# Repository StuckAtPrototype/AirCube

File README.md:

# AirCube

**See your air.** AirCube is a desktop air quality monitor with built-in **Home Assistant** support over **Zigbee** or **Bluetooth (BLE)**. Every model tracks temperature, humidity, eCO2, eTVOC, and VOC Level; AirCube Pro also measures true CO2 and ambient light. A glanceable LED shows the current air quality.

Works standalone out of the box. Pairs with Home Assistant in minutes. Other platforms are supported through **[community-contributed extensions](#community-extensions)**.

[AirCube Web](https://stuckatprototype.github.io/AirCube/) -- Live readings, history and firmware updates in your browser. Nothing to install.

[Watch the overview](https://www.youtube.com/watch?v=a4EFVtmDL8s) -- What AirCube does and why it's open source, in under three minutes.

[StuckAtPrototype Labs](https://www.youtube.com/@StuckAtPrototypeLabs) -- Step-by-step video walkthroughs: [ZHA setup](https://www.youtube.com/watch?v=rpkR3O64rY8), [Zigbee2MQTT setup](https://www.youtube.com/watch?v=eybU8-ZFDcc), and [updating firmware from the browser](https://www.youtube.com/watch?v=4XfEABJolAE).

[AirCube](https://stuckatprototype.com/products/aircube) -- Assembled AirCube

[AirCube Populated PCB](https://stuckatprototype.com/products/aircube-populated-pcb) -- AirCube Populated PCB

---

## Getting Started

**1. Plug it in** -- Connect the USB-C cable to any USB port or charger. AirCube powers on automatically.

**2. Wait for warm-up** -- The air quality sensor needs about 3 minutes to stabilize after power-on. During this time, the LED may not reflect accurate readings.

**3. Read the color** -- Once warmed up, the LED tells you everything:

| LED Color | Air Quality |
|-----------|------------|
| Green | Good |
| Yellow | Moderate |
| Orange | Poor |
| Red | Bad -- consider ventilating |

The color shifts smoothly as conditions change. No app needed -- just glance at it.

> **Firmware 1.5.0 and above** drive the LED from **canonical VOC Level** (TVOC-derived, absolute). The color is a smooth green-to-red gradient -- same feel as older firmware, but tied to fixed indoor-air bands instead of the relative AQI-S baseline. See **[LED Reference](#led-reference)** for the exact mapping. Firmware **1.4.3 and below** used the same gradient shape, but driven by **AQI-S** instead.

**4. Adjust brightness** -- Press the button to cycle through brightness levels.

That's it. AirCube works out of the box with no setup, no accounts, and no Wi-Fi.

---

## Base vs. Pro

Both models use the ScioSense ENS161 for VOC Level, eCO2, and eTVOC. Choose **Pro** when you also want a direct CO2 measurement and automatic LED dimming based on room light.

| Feature | Base | Pro |
|---------|------|-----|
| VOC Level, eCO2, and eTVOC | ENS161 | ENS161 |
| Temperature and humidity | ENS210 | Sensirion SCD41 |
| True CO2 | -- | Sensirion SCD41 (NDIR) |
| Ambient light | -- | VCNL4040 |
| Automatic LED dimming | -- | Yes |
| LED air-quality source | VOC Level | Whichever is worse: VOC Level or true CO2 |

> **eCO2 vs. true CO2:** eCO2 is an estimate derived from detected VOCs. The Pro's SCD41 measures CO2 directly using NDIR, while the ENS161 still detects odors and fumes that a pure CO2 sensor can miss.

## What AirCube Measures

| Measurement | Range | What It Tells You |
|-------------|-------|------------------|
| **VOC Level** | 0 -- 500 | TVOC-derived score against fixed indoor-air bands (firmware 1.5.0+; 0--500 scale in 1.5.1+) |
| **AQI-S** (deprecated) | -- | Legacy relative VOC score. As of firmware 1.5.0 this always reports **0** over USB serial -- kept only for compatibility. Use VOC Level instead. |
| **eCO2** (equivalent CO2) | 400 -- 65,000 ppm | Estimated CO2 level derived from detected VOCs |
| **CO2** (Pro only) | 400 -- 5,000 ppm | True CO2 concentration from the SCD41 (direct NDIR measurement) |
| **eTVOC** (equivalent Total VOC) | 0 -- 65,000 ppb | Total volatile organic compound concentration |
| **Temperature** | | Room temperature in Celsius |
| **Humidity** | 0 -- 100 % | Relative humidity percentage |
| **Illuminance** (Pro only) | | Ambient light in lux; also used to dim the LED automatically |

### Understanding the readings

AirCube Base uses a **ScioSense ENS161** gas sensor and an **ENS210** temperature/humidity sensor. AirCube Pro uses the ENS161 alongside an **SCD41** for true CO2, temperature, and humidity, plus a **VCNL4040** ambient light sensor.

**eCO2 (ppm)** -- Estimated CO2 derived from detected VOCs, not a direct CO2 measurement. Useful for judging ventilation; also picks up odors and fumes a pure CO2 sensor would miss.

**eTVOC (ppb)** -- Total volatile organic compounds in the air. Spikes after cooking or cleaning are normal; sustained high readings mean you should ventilate.

**VOC Level (0--500)** -- TVOC mapped to a fixed indoor-air scale (firmware 1.5.1+). Linear ramp between band edges; TVOC-only (eCO2 does not affect VOC Level). Reported over Zigbee and USB serial.

| Rating | LED color | VOC Level | TVOC (ppb) |
|--------|-----------|-----|------------|
| Excellent | Green | 0 -- 15 | 0 -- 65 |
| Good | Green → lime | 15 -- 50 | 65 -- 220 |
| Moderate | Lime → yellow | 50 -- 100 | 220 -- 650 |
| Poor | Yellow → orange → red | 100 -- 200 | 650 -- 2,200 |
| Unhealthy | Red | 200 -- 500 | 2,200 -- 5,500 |

On Base hardware, the LED color is derived from TVOC/VOC Level alone (eCO2 does not drive the LED). VOC Level is linear between band edges, so the LED fades smoothly. See below for Pro's CO2 arbitration.

**AQI-S (deprecated, USB serial only)** -- A legacy ScioSense relative score from firmware before 1.5.0. As of firmware 1.5.0, AQI-S is deprecated and always reports **0** -- it's kept in the serial output only for compatibility with older tools. Use **VOC Level**, **eCO2**/**eTVOC**, or true **CO2** (Pro) instead.

**VOC Level** drives the LED color on Base hardware. On **Pro**, the LED shows whichever is worse -- VOC Level or CO2 Level (from the true CO2 reading). See **[LED Reference](#led-reference)**.

### Warm-up and initial start-up

The ENS161 needs about **3 minutes** of warm-up in standard mode before readings stabilize. On the very first power-on of a new sensor the initial start-up takes about **1 hour** as the sensor conditions itself. Readings during these periods may be inaccurate -- the LED and status flag will indicate when the sensor is ready.

---

## Built-in vs. community

**Maintained by StuckAtPrototype:** firmware, hardware, desktop app, and the **Home Assistant** integration documented in **[HOME_ASSISTANT.md](HOME_ASSISTANT.md)**.

**Community-contributed:** integrations built and shared by the community. They live in this repo and are welcome, but StuckAtPrototype does not test or ship them. They may require extra setup and can break when a vendor updates their platform. See **[Community extensions](#community-extensions)**.

---

## Home Assistant Integration

AirCube was designed for Home Assistant. It connects over **Zigbee** -- no USB cable to your server, no cloud, no Wi-Fi credentials to configure. Plug it in, hold the button for 3 seconds to start pairing, and six core entities show up: temperature, humidity, eCO2, eTVOC, VOC Level, and brightness.

**AirCube Pro** adds two more: **true CO2** (SCD41) and **illuminance** (VCNL4040). Both are exposed in **ZHA** and **Zigbee2MQTT 2.x** -- eight entities total on a Pro.

Once connected you can:
- **Track air quality over time** with built-in history graphs
- **Set up automations** -- turn on a fan when eCO2 gets too high, send a notification when VOC Level spikes
- **Monitor every room** -- each AirCube pairs independently, name them however you like

**You'll need:** a Zigbee coordinator dongle (we recommend the [SONOFF ZBDongle-E](https://sonoff.tech/product/gateway-and-sensors/sonoff-zigbee-3-0-usb-dongle-plus-e/), ~$13) plugged into your Home Assistant machine.

**Works with** ZHA (built-in) and Zigbee2MQTT.

**Video walkthroughs:** [Set up AirCube with ZHA](https://www.youtube.com/watch?v=rpkR3O64rY8) · [Set up AirCube with Zigbee2MQTT](https://www.youtube.com/watch?v=eybU8-ZFDcc)

**Full setup guide:** **[Connecting AirCube to Home Assistant](HOME_ASSISTANT.md)**

### No Zigbee dongle? AirCube also works over Bluetooth

AirCube boots into **BLE mode** by default (until you pair it to Zigbee) and broadcasts standard
**BTHome** data -- temperature, humidity, CO2, and TVOC. If your Home Assistant instance has a
Bluetooth adapter or an [ESPHome Bluetooth proxy](https://esphome.io/components/bluetooth_proxy.html)
nearby, it can often pick up these readings passively, with no pairing step and no Zigbee hardware
at all. Building a custom BLE client? See the **[BLE GATT Protocol reference](docs/BLE_GATT_PROTOCOL.md)**.

---

## Community extensions

The integrations below are **community-contributed**. They are not maintained by StuckAtPrototype and compatibility with vendor hub or app updates is not guaranteed.

### SmartThings (Samsung Zigbee hub) — community-contributed

Some users run AirCube on a **Samsung SmartThings** Zigbee hub over **Zigbee** (no Wi-Fi configuration on the device). The hub must support **SmartThings Edge**.

By default, the SmartThings app may only show **temperature** and **humidity** until you install the community **AirCube Zigbee** Edge driver from this repository and assign it to the device.

**Full setup guide:** **[Connecting AirCube to SmartThings](SMARTTHINGS.md)** (pairing, SmartThings CLI, driver channel, verification in the app and [Advanced Web App](https://my.smartthings.com/advanced)).

**Troubleshooting:** If you only see temperature and humidity, install the **AirCube Zigbee** Edge driver from [`smartthings/aircube-zigbee/`](smartthings/aircube-zigbee/) and assign it to the device. Details are in **[SMARTTHINGS.md](SMARTTHINGS.md)**.

---

## Connect to Your Computer

Plug the AirCube into your computer with a **data-capable USB-C cable** to see live readings, charts, and history.

### In your browser -- nothing to install

**[AirCube Web](https://stuckatprototype.github.io/AirCube/)** connects over USB straight from Chrome or Edge: live readings, LED brightness, history with CSV export, and firmware updates. Click **Connect**, pick your cube, and you're in.

### Download the app

Check the [Releases](https://github.com/StuckAtPrototype/AirCube/releases) page for a ready-to-run Windows `.exe` -- no install required.

### Or run from source

```
git clone https://github.com/StuckAtPrototype/AirCube.git
cd AirCube/scripts
pip install -r requirements.txt
python aircube_app.py
```

Select your serial port, click **Connect**, and you'll see live data.

> **Tip:** Prefer a minimal taskbar-only view? See the companion [**AirCube Tray**](https://github.com/StuckAtPrototype/AirCubeTray) repo -- a lightweight Windows system-tray app that shows VOC Level as a live, color-coded number in your taskbar. It ships its own installer.

---

## Firmware Updates

The current firmware is **v2.0.7**. It keeps the cube responsive when plugged into a charger or closed port, and on Pro units it disables SCD41 automatic self-calibration (replaced by a 425 ppm fresh-air calibration) and detects a CO2 channel that has stopped reporting. See the [v2.0.7 release notes](releases/RELEASE_NOTES_v2.0.7.md).

**[Flash it now with AirCube Web](https://stuckatprototype.github.io/AirCube/)** or read the **[Firmware Update Guide](FIRMWARE_UPDATE.md)** for step-by-step instructions.

**Video walkthrough:** [Updating the AirCube is easy (web UI)](https://www.youtube.com/watch?v=4XfEABJolAE) -- under two minutes, start to finish.

All releases: [GitHub Releases](https://github.com/StuckAtPrototype/AirCube/releases)

---

## Assembling Your AirCube

Building one yourself from printed parts and a populated PCB? All you need is three M2 x 5 mm screws and a small Phillips screwdriver -- about ten minutes of work.

**[Assembly Guide](ASSEMBLY.md)** -- photo walkthrough for both Base and Pro.

Printable enclosure files live in [`mechanical/base/`](mechanical/base) and [`mechanical/pro/`](mechanical/pro).

---

## LED Reference

### Firmware 1.5.0 and above

The LED is a continuous green-to-red gradient driven by **canonical VOC Level** (TVOC-derived). The hue moves linearly with VOC Level: pure green up to VOC Level 10, then fading green → lime → yellow → orange → red, reaching full red at VOC Level 200. eCO2 does **not** affect the LED.

```mermaid
flowchart LR
    A["VOC Level 0–10<br/>TVOC 0–~43 ppb"] --> G["Steady green"]
    B["VOC Level 10–200<br/>TVOC ~43–2 200 ppb"] --> GR["Green → lime → yellow → orange → red"]
    C["VOC Level 200+<br/>TVOC 2 200+ ppb"] --> R["Steady red"]
```

| LED color | VOC Level | TVOC (ppb) | Rating |
|-----------|-----|------------|--------|
| Steady green | 0 -- 10 | 0 -- ~43 | Excellent |
| Green → lime | 10 -- 50 | ~43 -- 220 | Good |
| Lime → yellow | 50 -- 100 | 220 -- 650 | Moderate |
| Yellow → orange → red | 100 -- 200 | 650 -- 2 200 | Poor |
| Steady red | 200+ | 2 200+ | Unhealthy |
| Flashing blue | -- | -- | Zigbee pairing mode |

Key gradient landmarks: **yellow** around VOC Level 105 (~730 ppb) and **orange** around VOC Level 150 (~1,460 ppb). Over **Zigbee**, TVOC-derived VOC Level is reported alongside eCO2, eTVOC, temperature, humidity, and brightness. **AQI-S** is deprecated, always reports 0, and does not drive the LED.

**On Pro hardware**, the LED shows whichever reading is worse: VOC Level (as above) or **CO2 Level**, a
0--500 score derived from the true SCD41 CO2 reading using the same band scale. If CO2 Level is
higher than VOC Level, the LED reflects the CO2 reading instead. On **Base** hardware, CO2 Level is
always 0, so VOC Level always drives the LED.

### Firmware 1.4.3 and below (legacy)

Same gradient shape as above, but driven by **AQI-S** (relative, 24-hour baseline) instead of canonical VOC Level:

| LED | Meaning |
|-----|---------|
| Steady green | Good air quality (AQI-S 0--10) |
| Yellow through red | Degrading to poor air quality (AQI-S 10--200) |
| Steady red | Poor air quality (AQI-S 200+) |
| Flashing blue | Zigbee pairing mode |

### Button

| Action | What It Does |
|--------|-------------|
| Short press | Cycle brightness (off, 10%, 30%, 60%, 100%) |
| Hold 3 seconds | Enter Zigbee pairing mode |

---

## Troubleshooting

**LED doesn't turn on**
- Make sure the USB-C cable is firmly connected and the power source is active.
- Try a different USB port or charger.

**Readings seem wrong right after power-on**
- Normal. The air quality sensor needs about 3 minutes to warm up. Readings will stabilize.

**Computer doesn't detect AirCube**
- Some USB cables are charge-only. Use a cable that supports data.
- Windows users may need to install [USB drivers](https://www.silabs.com/developers/usb-to-uart-bridge-vcp-drivers).
- Linux users: add yourself to the `dialout` group and re-login.

**Home Assistant: eCO2, TVOC, or VOC Level sensors are missing**
- The custom quirk or converter isn't loaded yet. See the [Home Assistant guide](HOME_ASSISTANT.md) for step-by-step instructions.

**Home Assistant: CO2 or Illuminance is missing (Pro)**
- These come from standard Zigbee clusters, so ZHA and Zigbee2MQTT 2.x pick them up without any extra configuration. If they're absent, confirm the unit is a Pro (Base has no SCD41 or VCNL4040), then remove and re-pair so the coordinator re-reads the endpoint. The legacy Zigbee2MQTT 1.x converter does not expose them.

**Home Assistant: AirCube won't pair**
- Make sure permit join is enabled in ZHA or Zigbee2MQTT.
- Hold the button for 3 seconds to enter pairing mode (LED flashes blue).
- Move AirCube closer to the coordinator during pairing.

---

## Open Source

AirCube is fully open source -- firmware, PCB design, enclosure, desktop software, and Home Assistant integration. Community-contributed integrations (see **[Community extensions](#community-extensions)**) also live in this repository. Everything is under the Apache 2.0 license.

**Developers and makers:** See the **[Contributing Guide](CONTRIBUTING.md)** for build instructions, architecture docs, serial protocol reference, and how to submit changes. Curious about the PCB? [These Holes Are Why My Circuit Board Works](https://www.youtube.com/watch?v=1yfeTHR3lqw) explains the cutouts in the board.

| | |
|---|---|
| [StuckAtPrototype Labs](https://www.youtube.com/@StuckAtPrototypeLabs) | Video walkthroughs: ZHA, Zigbee2MQTT, firmware updates |
| [Contributing Guide](CONTRIBUTING.md) | Build from source, firmware architecture, serial protocol, how to contribute |
| [Assembly Guide](ASSEMBLY.md) | Assemble the printed enclosure -- Base and Pro |
| [BLE GATT Protocol](docs/BLE_GATT_PROTOCOL.md) | BLE GATT protocol reference for building custom BLE clients |
| [Firmware Update Guide](FIRMWARE_UPDATE.md) | Update your AirCube firmware from a browser |
| [AirCube Web](web/) | The browser app: Web Serial monitoring, settings and flashing |
| [Home Assistant Guide](HOME_ASSISTANT.md) | ZHA and Zigbee2MQTT setup |
| [Samsung hub integration](SMARTTHINGS.md) | Community-contributed: Edge driver, CLI setup (see **[Community extensions](#community-extensions)**) |
| [GitHub Issues](https://github.com/StuckAtPrototype/AirCube/issues) | Bug reports and feature requests |
| [License](LICENSE) | Apache 2.0 |

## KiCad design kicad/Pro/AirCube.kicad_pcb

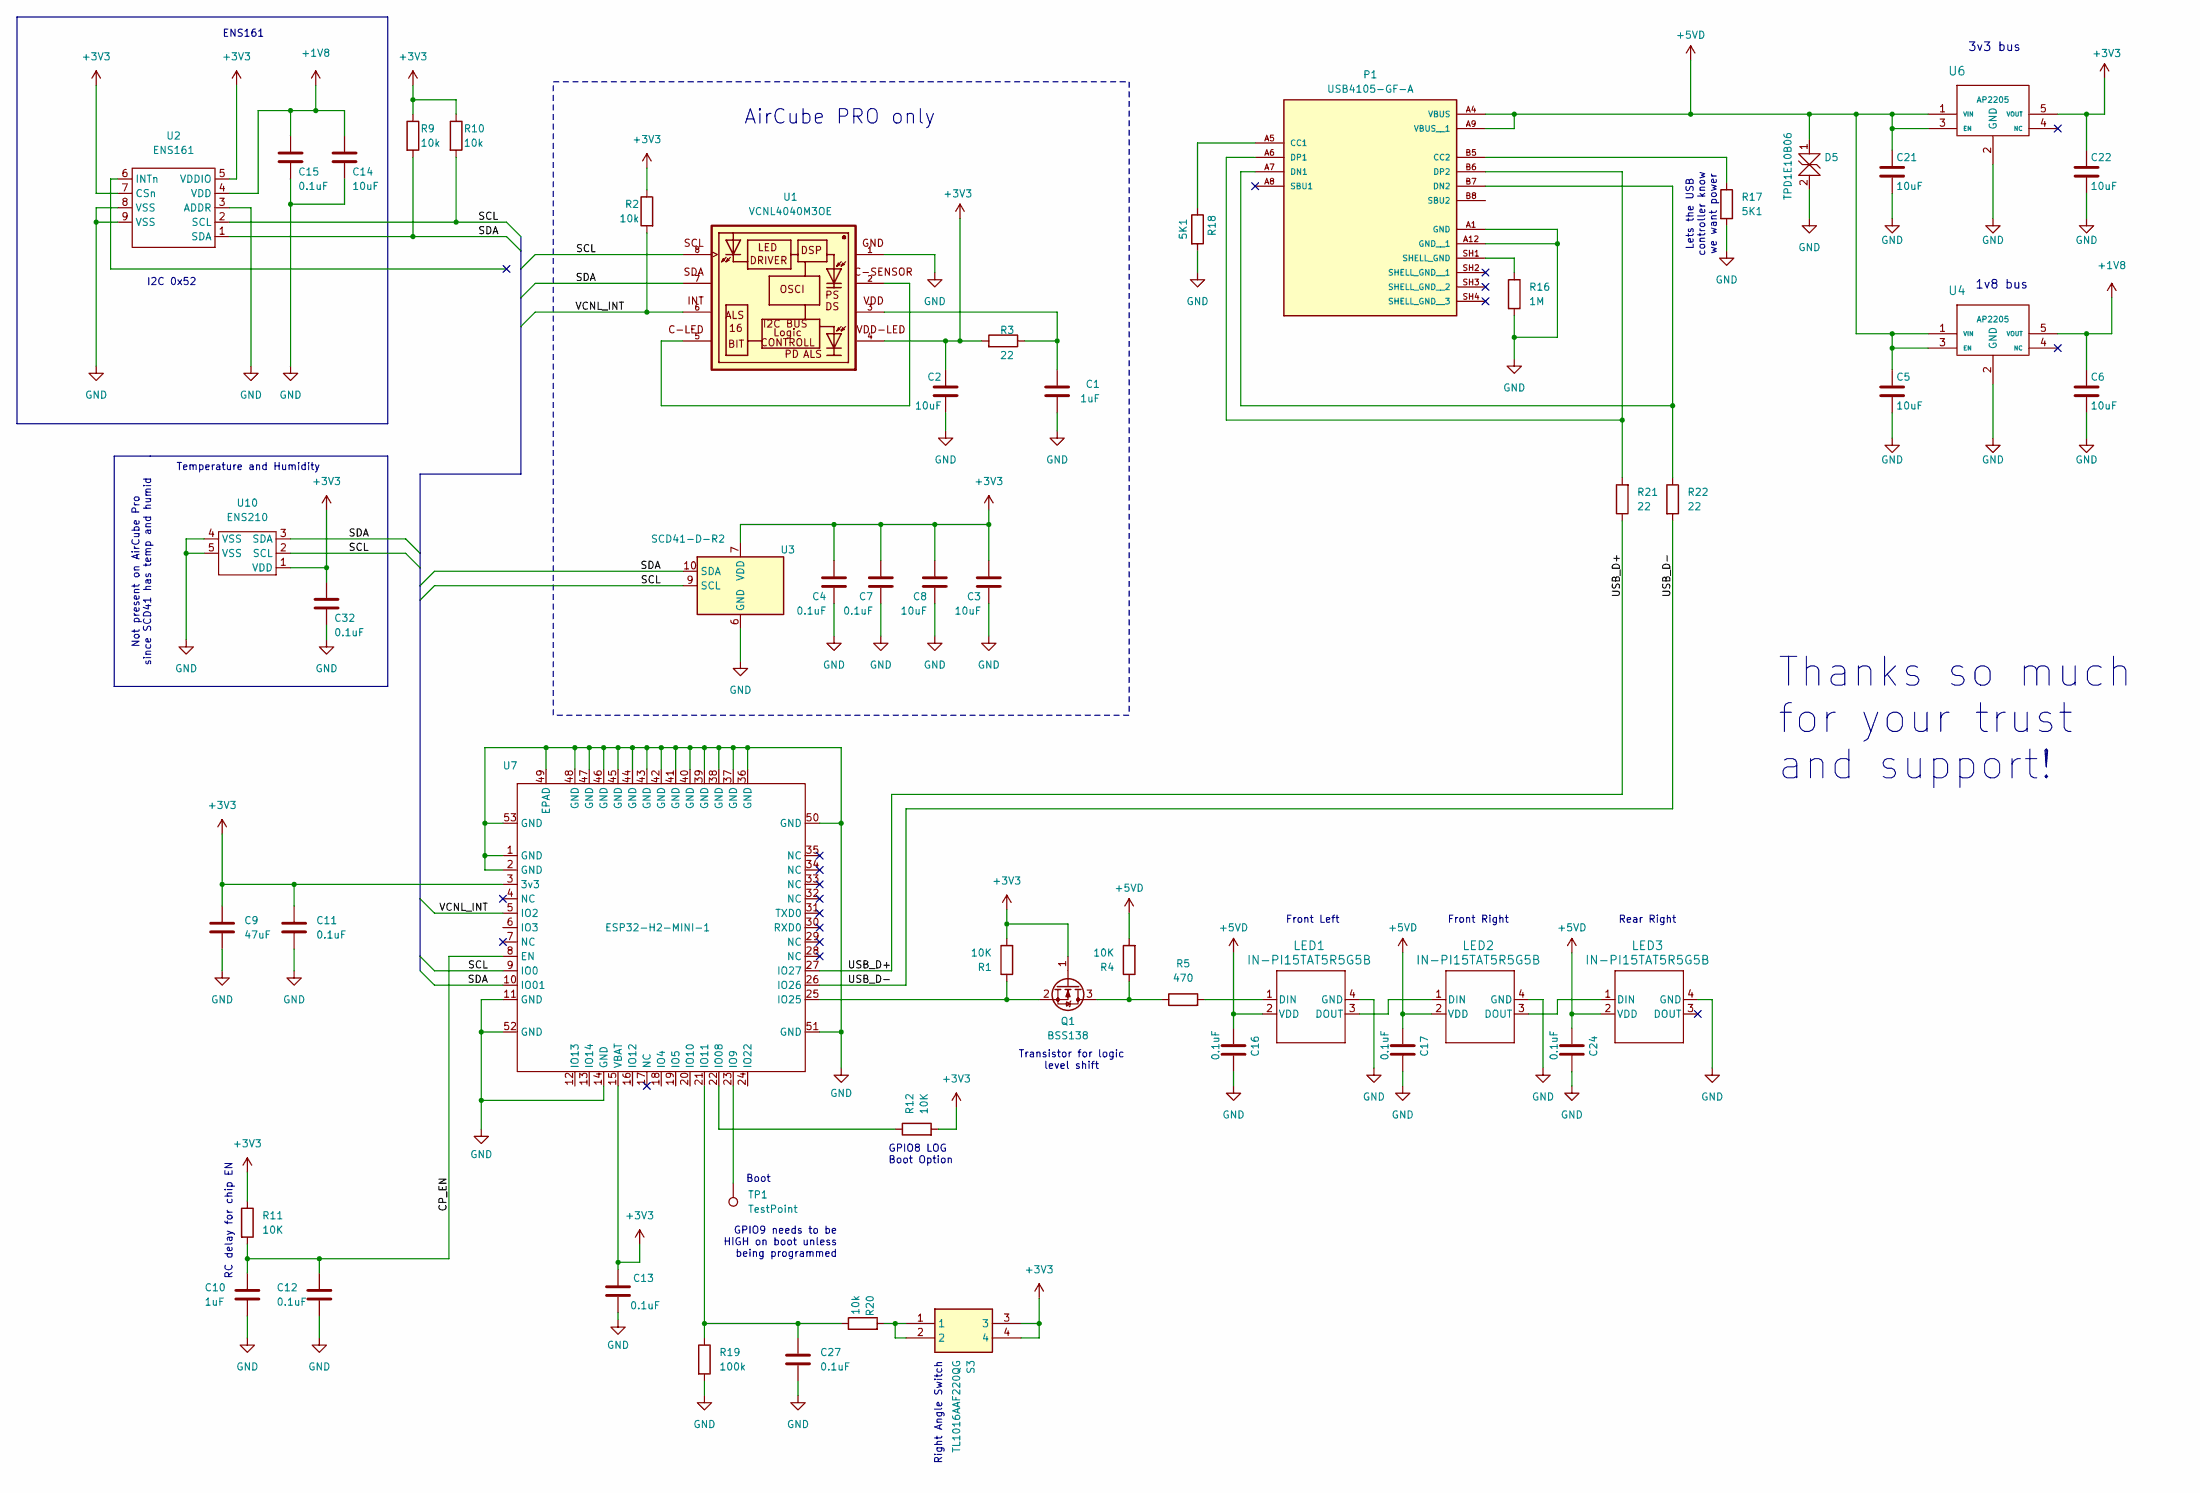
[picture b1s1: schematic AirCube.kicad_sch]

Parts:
C1, C10: 1uF; C_0603_1608Metric
C2, C3, C5, C6, C8, C14, C21, C22: 10uF; C_0603_1608Metric
C4, C7, C11, C12, C13, C15, C16, C17, C24, C27, C32: 0.1uF; C_0603_1608Metric
C9: 47uF; C_0603_1608Metric
D5: TPD1E10B06; D_SOD-523
LED1, LED2, LED3: IN-PI15TAT5R5G5B; IN-PI15_INL
P1: USB4105-GF-A; GCT_USB4105-GF-A; PARTREV B4
Q1: BSS138; SOT-23
R1, R4, R11, R12: 10K; R_0603_1608Metric
R2, R9, R10, R20: 10k; R_0603_1608Metric
R3, R21, R22: 22; R_0603_1608Metric
R5: 470; R_0603_1608Metric
R16: 1M; R_0603_1608Metric
R17, R18: 5K1; R_0603_1608Metric
R19: 100k; R_0603_1608Metric
S3: TL1016AAF220QG; Mouser Part Number 612-TL1016AAF220QG
TP1: TestPoint; TestPoint_Pad_D1.0mm
U1: VCNL4040M3OE; VISHAY_VCNL4040_4X2X1.1
U2: ENS161
U3: SCD41-D-R2; Sensirion_SCD4x-1EP_10.1x10.1mm_P1.25mm_EP4.8x4.8mm
U4, U6: AP2205; AP2204
U7: ESP32-H2-MINI-1; MODULE_ESP32-H2-MINI-1-H2
U10: ENS210

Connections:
+1V8: C6.1, C14.1, C15.1, U2.4 (VDD), U4.5 (VOUT)
+3V3: C2.1, C3.1, C4.1, C7.1, C8.1, C9.1, C11.1, C13.1, C22.1, C32.1, Q1.1 (G), R1.2, R2.1, R3.2, R9.1, R10.1, R11.1, R12.2, S3.3, S3.4, U1.4, U2.5 (VDDIO), U2.7 (CSn), U3.7 (VDD), U3.19 (VDD), U6.5 (VOUT), U7.3 (3v3), U7.15 (VBAT), U10.1 (VDD)
+5VD: C5.1, C16.1, C17.1, C21.1, C24.1, D5.1, LED1.2 (VDD), LED2.2 (VDD), LED3.2 (VDD), P1.A4 (VBUS), P1.A9 (VBUS__1), R4.2, U4.1 (VIN), U4.3 (EN), U6.1 (VIN), U6.3 (EN)
/CP_EN: C10.1, C12.1, R11.2, U7.8 (EN)
/SCL: R10.2, U1.8, U2.2 (SCL), U3.9 (SCL), U7.9 (IO0), U10.2 (SCL)
/SDA: R9.2, U1.7, U2.1 (SDA), U3.10 (SDA), U7.10 (IO01), U10.3 (SDA)
/USB_D+: R21.1, U7.27 (IO27)
/USB_D-: R22.2, U7.26 (IO26)
/VCNL_INT: R2.2, U1.6, U7.5 (IO2)
GND: C1.2, C2.2, C3.2, C4.2, C5.2, C6.2, C7.2, C8.2, C9.2, C10.2, C11.2, C12.2, C13.2, C14.2, C15.2, C16.2, C17.2, C21.2, C22.2, C24.2, C27.2, C32.2, D5.2, LED1.4 (GND), LED2.4 (GND), LED3.4 (GND), P1.A1 (GND), P1.A12 (GND__1), R16.2, R17.2, R18.2, R19.2, U1.1, U2.3 (ADDR), U2.8 (VSS), U2.9 (VSS), U3.6 (GND), U3.20 (GND), U3.21 (GND), U4.2 (GND), U6.2 (GND), U7.1 (GND), U7.2 (GND), U7.11 (GND), U7.14 (GND), U7.36 (GND), U7.37 (GND), U7.38 (GND), U7.39 (GND), U7.40 (GND), U7.41 (GND), U7.42 (GND), U7.43 (GND), U7.44 (GND), U7.45 (GND), U7.46 (GND), U7.47 (GND), U7.48 (GND), U7.49 (EPAD), U7.50 (GND), U7.51 (GND), U7.52 (GND), U7.53 (GND), U10.4 (VSS), U10.5 (VSS)
unnamed: C1.1, R3.1, U1.3
unnamed: LED1.1 (DIN), R5.2
unnamed: LED1.3 (DOUT), LED2.1 (DIN)
unnamed: LED2.3 (DOUT), LED3.1 (DIN)
unnamed: P1.A5 (CC1), R18.1
unnamed: P1.B5 (CC2), R17.1
unnamed: P1.A7 (DN1), P1.B7 (DN2), R22.1
unnamed: P1.A6 (DP1), P1.B6 (DP2), R21.2
unnamed: P1.SH1 (SHELL_GND), R16.1
unnamed: Q1.3 (D), R4.1, R5.1
unnamed: Q1.2 (S), R1.1, U7.25 (IO25)
unnamed: R20.2, S3.1, S3.2
unnamed: U1.2, U1.5
unnamed: R12.1, U7.22 (IO08)
unnamed: TP1.1, U7.23 (IO9)
unnamed: C27.1, R19.1, R20.1, U7.21 (IO11)

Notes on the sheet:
Not present on AirCube Pro since SCD41 has temp and humid
Rear Right
AirCube PRO only
Transistor for logic level shift
GPIO8 LOG Boot Option
Boot
Thanks so much for your trust and support!
Right Angle Switch
Lets the USB controller know we want power
Front Right
ENS161
3v3 bus
GPIO9 needs to be HIGH on boot unless being programmed
Front Left
I2C 0x52
RC delay for chip EN
1v8 bus
Temperature and Humidity

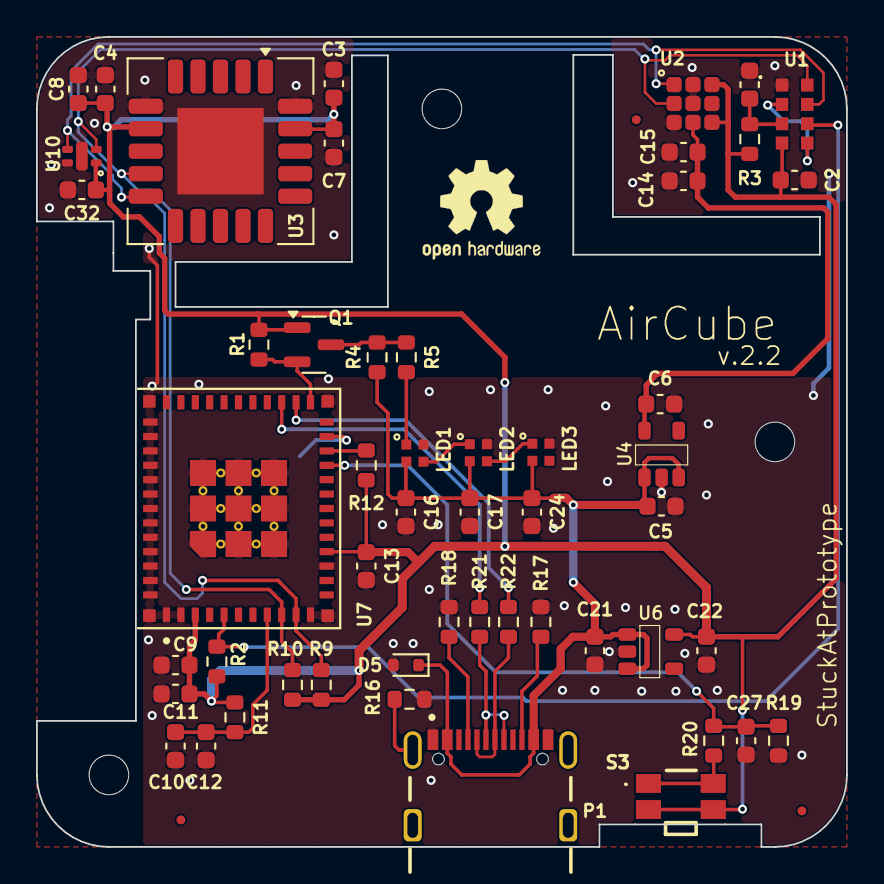
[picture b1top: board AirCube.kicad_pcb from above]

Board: 2 copper layers, 45.0 x 45.0 mm, 53 parts (1 on the bottom side), 26 nets.

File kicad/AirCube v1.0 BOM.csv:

Id,Designator,Footprint,Quantity,Designation,Supplier and ref,
1,"R10,R20,R9",R_0603_1608Metric,3,10k,WR06X103 JTL,
2,"C15,C24,C13,C17,C12,C16,C32,C27,C11",C_0603_1608Metric,9,0.1uF,CC0603KRX7R7BB104,
3,U7,MODULE_ESP32-H2-MINI-1-H2,1,ESP32-H2-MINI-1,ESP32-H2-MINI-1,
4,"LED1,LED2,LED3",IN-PI15_INL,3,IN-PI15TAT5R5G5B,IN-PI15TAT5R5G5B,
5,U10,ENS210,1,ENS210,ENS210-LQFM,
6,"R18,R17",R_0603_1608Metric,2,5K1,RC0603FR-075K1L,
7,"C14,C23,C22,C21",C_0603_1608Metric,4,10uF,GRM188R61A106ME69D,
8,R5,R_0603_1608Metric,1,470,ESR03EZPF4700,
9,R19,R_0603_1608Metric,1,100k,WR06X1003FTL,
10,"R11,R4,R12,R1",R_0603_1608Metric,4,10K,WR06X103 JTL,
11,U5,SOT-23,1,AP2120,AP2120N-1.8TRG1,EOL
12,D5,D_SOD-523,1,TPD1E10B06,TPD1E10B06DYAR,
13,"R21,R22",R_0603_1608Metric,2,22,RC0603JR-0722RL,
14,U6,AP2204,1,AP2205,AP2205-33W5-7,
15,P1,GCT_USB4105-GF-A,1,USB_C_Plug_USB2.0,USB4105-GF-A,
16,"C5,C10",C_0603_1608Metric,2,1uF,CC0603KRX5R8BB105,
17,R16,R_0603_1608Metric,1,1M,RMCF0603FT1M00,
18,S2,SWITCH_0SMTRLFS,1,SWITCH_0SMTRLFS,RKB2SJK250SMTR LFS,
19,U2,ENS161,1,ENS161,ENS161-BLGT LGA9 T&R 1k5,
20,S3,TL1016AAF220QG,1,TL1016AAF220QG,TL1016AAF220QG,
21,Q1,SOT-23,1,BSS138,BSS138,
22,C9,C_0603_1608Metric,1,47uF,GRM188C80E476ME05D,

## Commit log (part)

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2025-11-11 init
2025-11-11 all sensors functional
2025-11-11 status bits and en210 is now written to ens161
2025-11-11 AQI to color mapping + threading
2025-11-11 adding pulsing blue color on warmup
2025-11-11 ens210 now works in continuous mode. serial protocol added in json format. leds are 30% default brightness
2025-11-11 working version
2025-11-12 - Changed AQI_MAX from 300 to 200 for faster color transition - Added red pulsing effect when AQI >= 200 to indicate dangerous air quality
2025-11-14 - Remove get_pulsing_color() from led_color_lib - Add get_pulsing_color_with_intensity() in main.c with intensity support - Update LED control logic to use new local pulsing function - Pulse period c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
2025-11-14 adding button led intensity toggle
2025-11-14 adding nvs functionality to remember the LED intensity the user has chosen
2025-11-14 shifting the color scale slightly for better visual representation.
2025-11-14 speeding up the led funciton and adding a hello animation
2025-11-14 adding a smooth color transition
2025-12-14 adding mechanicals, scripts, kicad files
2025-12-14 adding a readme and license
2026-02-02 adding a standalone python app for the aircube
2026-02-03 adding a aircube_tray windows program. adding one more level of brightness. fixing ens status drivers
2026-02-07 Home Assistant Zigbee functional!
2026-02-07 homeassistant guide and HA scripts
2026-02-08 history is now saved to flash. we are saving min/max/avg every 10 minutes. we are keeping about 14 days of data in a circular buffer. with this wear, flash should last 1k+ years
2026-02-23 Add AQI-UBA to serial/tray, 5-min history window, Live/History/Serial tabs, hover tooltips, and history progress/refresh
2026-03-03 updaing aircube tray program
2026-03-03 updaing the readmes to make it easier to read and include home assistant mention
2026-03-04 hotfix. compilation and partition problems
2026-03-04 fixing HA pairing and factory reset
2026-03-04 adding a firmware update doc
2026-03-06 adding a power setting to zigbee
2026-03-07 making sure we are displaying eCO2, not CO2
2026-03-13 Add Z2M 2.x external converter (.mjs) for AirCube
    Z2M 2.x requires ES module format (.mjs) — the existing CommonJS
    converter (aircube.js) fails to load silently (renamed to .invalid).
    Two additional Z2M 2.x compatibility fixes in the new converter:
    - Cluster ID must be a string ('64513') not a number (0xFC01),
    because Z2M 2.x compares unknown cluster names as strings
    - Import paths use no .js extension per Z2M 2.x conventions
2026-03-14 Fix AirCube ZHA quirk import
2026-03-14 Expose firmware version via Zigbee SWBuildID
2026-03-20 updating readme to correctly reflect all metions of eCO2
2026-03-23 adding debug info for zigbee
2026-03-23 throttling the zigbee connection to every 10 seconds
2026-03-24 adding brightness level. replacing v1 quirks with v2 inports for 2026 compatibility
2026-03-24 works!
2026-03-26 updaing docs
2026-03-26 docs update
2026-03-26 configuration path needs a / at the end for HA 2026
2026-03-27 updating docs to better explain 2025 vs 2026 diffs
2026-03-29 Resize partition table for 2MB flash, track in git
    Shrink app partition from 3MB to 1.6MB so the same binary runs on both 2MB and 4MB flash boards. Add gitignore exception for the partition table CSV.
    Made-with: Cursor
2026-04-08 adding SmartThings Edge driver and setup guide
2026-04-08 updating SmartThings channel setup to use driver-channel.json and stuckatprototype tos url
2026-04-08 updating readme, contributing, and smartthings docs for driver-channel.json
2026-04-11 Added a temporary solution to the v1.3 released bin, and some extra docs on what is going on in this repo, homeassistant docs from my personal setup
2026-04-12 button task needed more ram
2026-04-12 fixing aqi mapping, firmware updates, copyright lines, and improving readme to clearly have a distinction between offically supported vs community made extensions
2026-04-12 softening the language in the readme
2026-04-12 updaing the readme to better explain what the device measures
2026-04-16 hot-fix automatic network rejoin bug
2026-04-16 fixing zigbee lockup
2026-04-16 .\firmware\version.txt
2026-04-22 removing the tray program from this repo and moving it into its own
2026-04-27 Leading slash in custom_quirks_path caused zha to fail startup
2026-04-28 Displays AQI in the Mac OS menu bar
2026-05-25 Round reported Zigbee brightness percentage
2026-05-29 fix(release): Updating to use semantic-release instead of scripts
2026-05-29 feat(build): Build GitHub actions (#4)
    * feat(releases): Adding release generation
    * build(idf): Update idf to 5.5.2
    * fix(workflow): Make sure to use the ESP toolchain setup
    * fix(workflow): CI also needs the ESP-IDF toolchain setup
    * fix(release): Updating to use semantic-release instead of scripts
2026-05-29 feat(zigbee): enable zigbee router (#5)
2026-05-29 fix(zigbee): Report the power source as DC
2026-06-02 add serial2mqtt script
2026-06-02 make publish interval configurable
